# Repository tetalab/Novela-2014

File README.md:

Novela-2014
===========

# Instructions Bristlebot

## Pièces nécessaires

* 1x PCB
* 2x leds
* 1x support de pile
* 1x pile bouton 2032
* 1x interrupteur
* 1x résistance 330 Ohms
* 1x moteur vibreur
* 1x brosse à dent
* 1x scotch double face (env 3cm)
* 2-6x segments de 4-8cm cable réseau

## Pas à pas

1. souder la résistance R1
1. poser un peu d'étain sur la grosse pastille où se trouvera la pile
1. souder le support de pile
1. souder l'interrupteur
1. souder le moteur
1. fixer le moteur au PCB avec le pistolet à colle
1. souder les leds, la patte la plus courte au niveau du symbole (-) sous le PCB
1. mettre du scotch double-face sous le PCB
1. casser une brosse à dent et fixer la partie poilue sous le scotch double-face
1. dénuder les morceaux de cables réseaux
1. souder ces segments de cable réseau au niveau des pattes

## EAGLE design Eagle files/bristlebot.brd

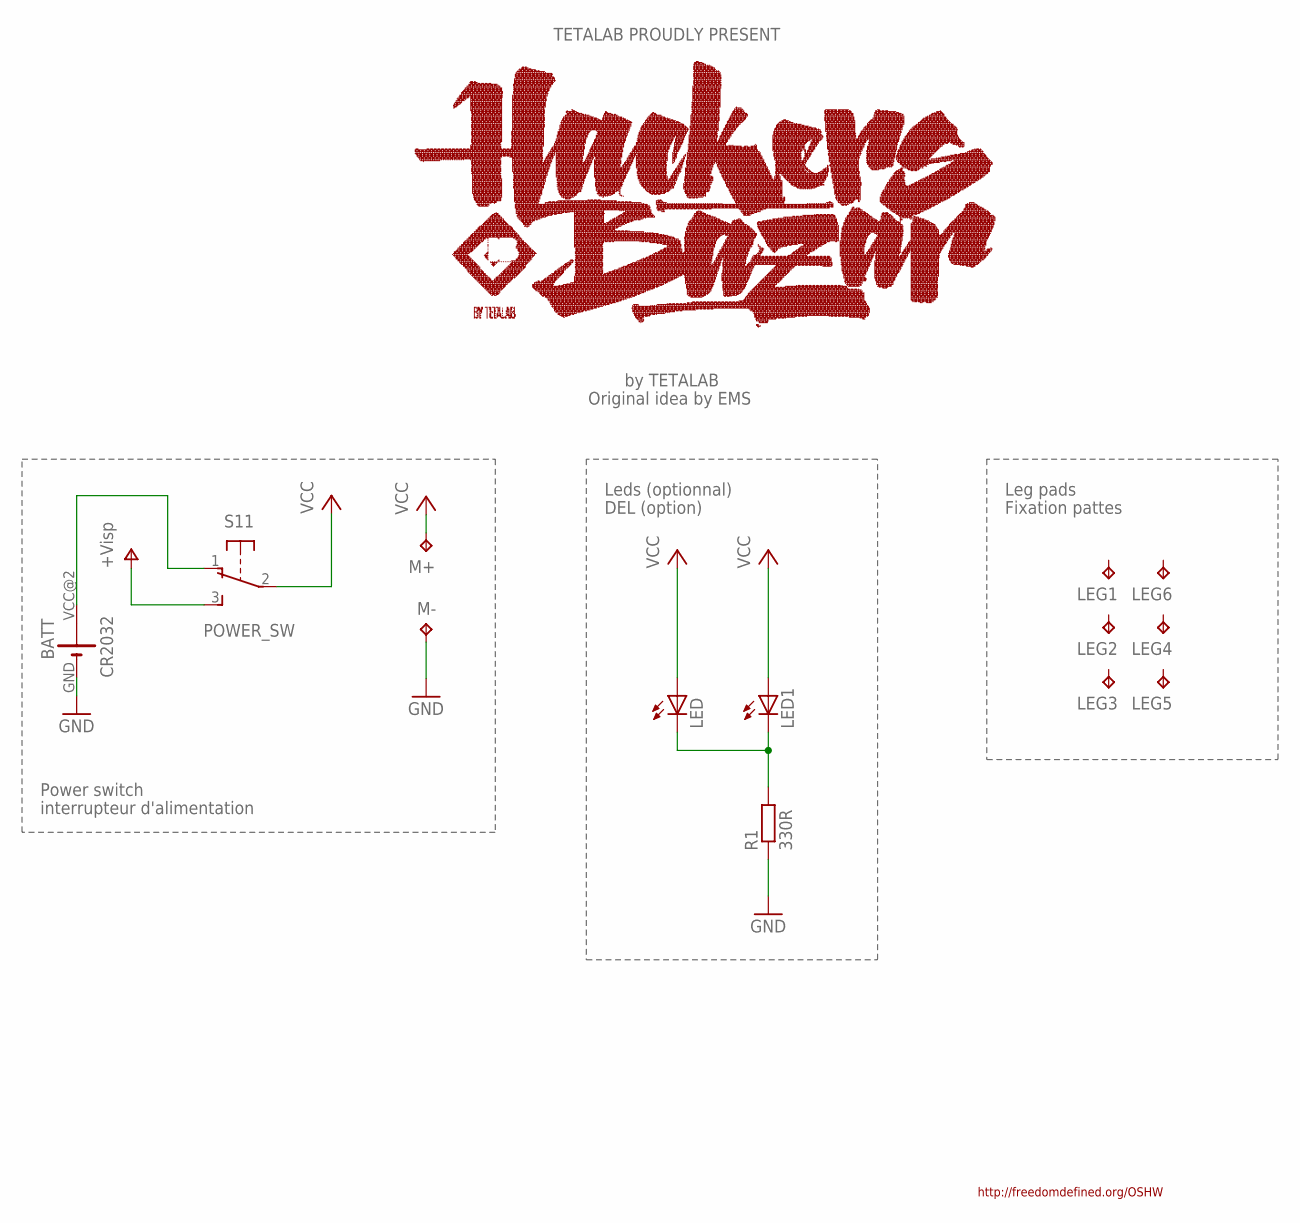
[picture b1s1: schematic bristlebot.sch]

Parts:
BATT: CR2032; BATT_CONN_CR2032
LED, LED1: LED3MM
LEG1, LEG2, LEG3, LEG4, LEG5, LEG6: TPPAD0.8-2.5R; P0.8-2.5
M+: TPPAD0.8-2R; P0.8-2
M-: TPPAD0.8-2R; P0.8-2
R1: 330R; 0207/7
S1: POWER_SW; OS102011MA1QN1

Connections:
GND: BATT.GND (-), M-.TP, R1.1
unnamed: LED.K (C), LED1.K (C), R1.2
V+: S1.3
VBAT: BATT.VCC@2 (+), S1.1
VCC: LED.A, LED1.A, M+.TP, S1.2

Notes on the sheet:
Power switch
interrupteur d'alimentation
Leds (optionnal)
DEL (option)
Original idea by EMS
by TETALAB
http://freedomdefined.org/OSHW
TETALAB PROUDLY PRESENT
Leg pads
Fixation pattes

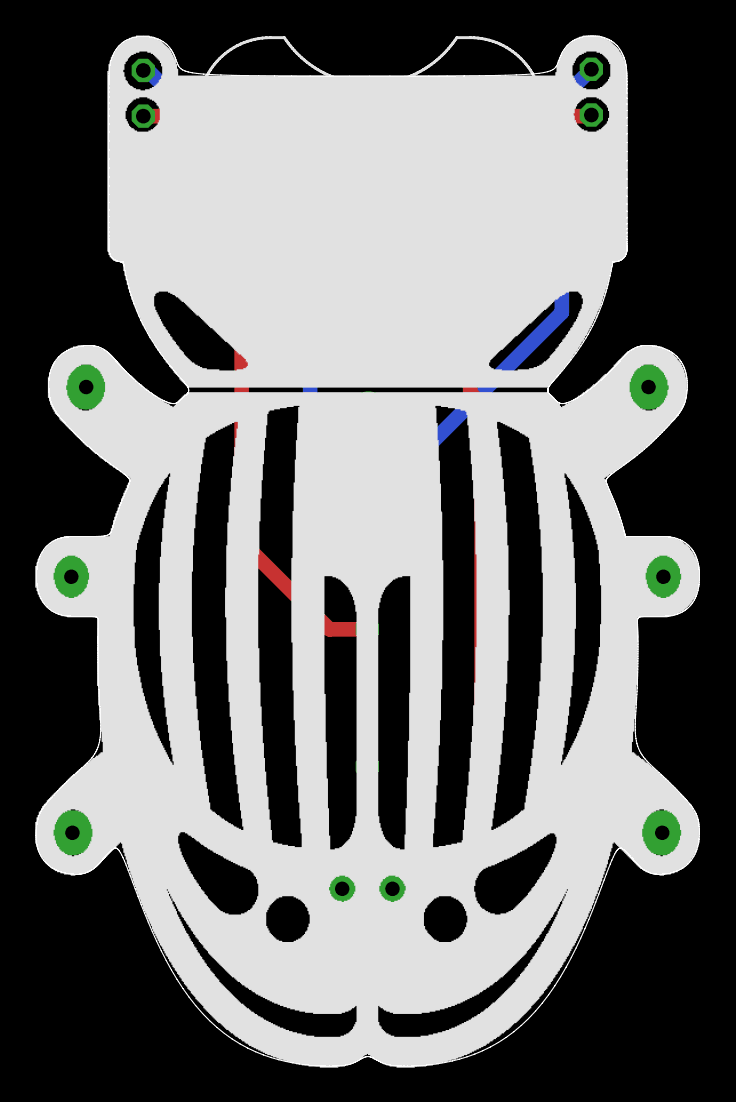
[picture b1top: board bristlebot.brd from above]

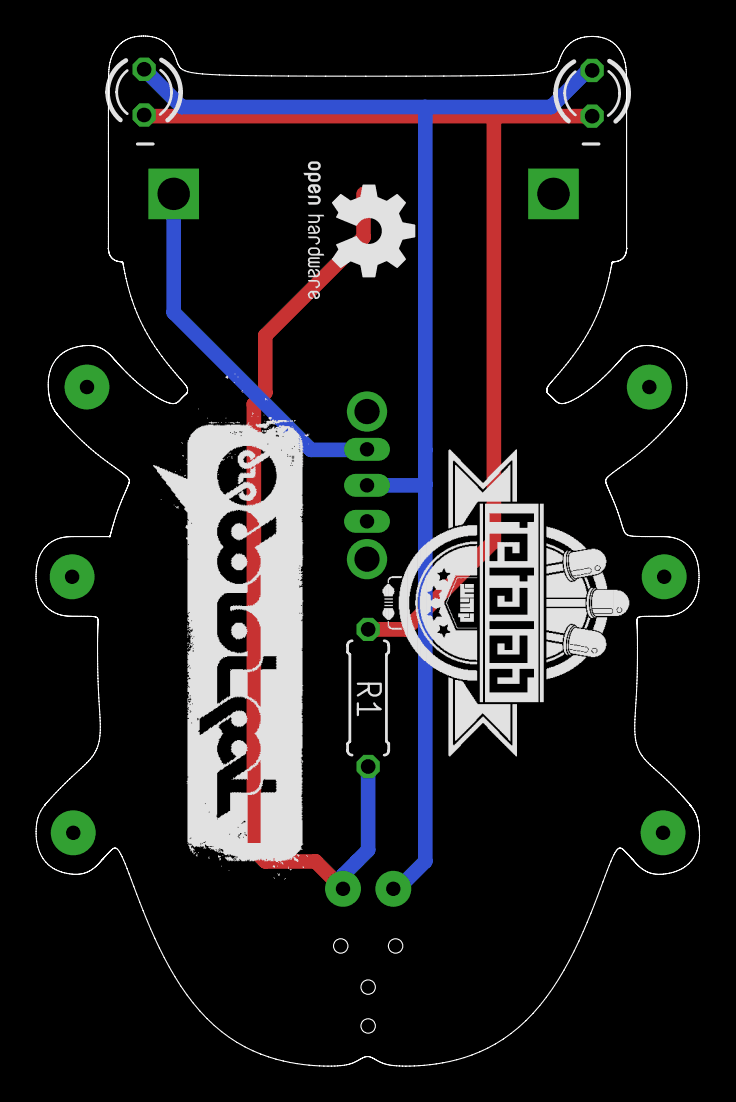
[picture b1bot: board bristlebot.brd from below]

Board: 2 copper layers, 36.9 x 57.2 mm, 14 parts (4 on the bottom side), 4 nets.

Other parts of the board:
U$1: LOGO_OH_FULL_H7

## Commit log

2014-11-06 Instruction bristlebot
2014-11-06 typo
2014-11-06 re-typo
2014-11-06 Bristlebot PCB & Gerber files - Eagle Cadsoft 6.4
2014-11-06 Add Eagle files Directory
    Add Eagle files Directory & move files
2014-11-06 R1 value added
2014-11-06 Add pdf & png schematics + pcb picture
